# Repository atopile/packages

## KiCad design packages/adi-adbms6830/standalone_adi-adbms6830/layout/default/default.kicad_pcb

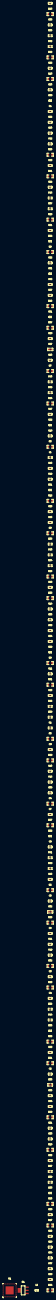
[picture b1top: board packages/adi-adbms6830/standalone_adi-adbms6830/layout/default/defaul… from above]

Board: 2 copper layers, 123 parts (0 on the bottom side), 82 nets, no tracks yet.

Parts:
C1, C2, C3, C4, C5, C6, C7, C8, C9, C10, C11, C12, C13, C14, C15, C16, C17, C18, C19, C20, C21, C22, C23, C24, C25, C26, C27, C28, C29, C30, C31, C32, C33, C34, C35, C36, C37, C38, C39, C40, C41, C42, C43, C44, C45, C46, C47, C48, C49, C50, C53, C54, C55, C56, C60: 0F; C0603
C51, C52, C58, C59, C61: 0F; C0402
C57, C62: 0F; C0805
L1: L 0H; L0603
L2: L0402
Q1: SOT-223-4_L6.5-W3.5-P2.30-LS7.0-BR
R1, R34, R35, R36, R37, R38, R39, R40, R41, R42, R43, R44, R45, R46, R47, R48, R49, R50: 200Ω; R0603
R2, R3, R4, R5, R6, R7, R8, R9, R10, R11, R12, R13, R14, R15, R16, R17, R18, R19, R20, R21, R22, R23, R24, R25, R26, R27, R28, R29, R30, R31, R32, R33: 22Ω; R1206
R51, R52, R53, R54: 49.9Ω; R0402
R55: 1000Ω; R0805
R56: 10Ω; R0402
R57: 330Ω; R1206
U1: QFN-72_L10.0-W10.0-P0.50-BL-EP6.0_1

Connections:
C0: C34.1, C35.2, R34.2, U1.50
C1: C35.1, C36.2, R35.2, U1.48
C2: C36.1, C37.2, R36.2, U1.45
C3: C37.1, C38.2, R37.2, U1.42
C4: C38.1, C39.2, R38.2, U1.39
C5: C39.1, C40.2, R39.2, U1.36
C6: C40.1, C41.2, R40.2, U1.33
C7: C41.1, C42.2, R41.2, U1.30
C8: C1.2, C42.1, R42.2, U1.27
C9: C43.1, C44.2, R43.2, U1.23
C9N: C1.1, C43.2, R1.2, U1.26
C10: C44.1, C45.2, R44.2, U1.20
C11: C45.1, C46.2, R45.2, U1.17
C12: C46.1, C47.2, R46.2, U1.14
C13: C47.1, C48.2, R47.2, U1.11
C14: C48.1, C49.2, R48.2, U1.8
C15: C49.1, C50.2, R49.2, U1.5
C16: C50.1, R50.2, U1.2
DRIVE: R56.1, U1.58
S1N: C2.1, C3.2, R2.2, U1.59
S1P: C3.1, C4.2, R3.2, U1.49
S2N: C4.1, C5.2, R4.2, U1.46
S2P: C5.1, C6.2, R5.2, U1.47
S3N: C6.1, C7.2, R6.2, U1.43
S3P: C7.1, C8.2, R7.2, U1.44
S4N: C8.1, C9.2, R8.2, U1.40
S4P: C9.1, C10.2, R9.2, U1.41
S5N: C10.1, C11.2, R10.2, U1.37
S5P: C11.1, C12.2, R11.2, U1.38
S6N: C12.1, C13.2, R12.2, U1.34
S6P: C13.1, C14.2, R13.2, U1.35
S7N: C14.1, C15.2, R14.2, U1.31
S7P: C15.1, C16.2, R15.2, U1.32
S8N: C16.1, C17.2, R16.2, U1.28
S8P: C17.1, C18.2, R17.2, U1.29
S9N: C18.1, C19.2, R18.2, U1.24
S9P: C19.1, C20.2, R19.2, U1.25
S10N: C20.1, C21.2, R20.2, U1.21
S10P: C21.1, C22.2, R21.2, U1.22
S11N: C22.1, C23.2, R22.2, U1.18
S11P: C23.1, C24.2, R23.2, U1.19
S12N: C24.1, C25.2, R24.2, U1.15
S12P: C25.1, C26.2, R25.2, U1.16
S13N: C26.1, C27.2, R26.2, U1.12
S13P: C27.1, C28.2, R27.2, U1.13
S14N: C28.1, C29.2, R28.2, U1.9
S14P: C29.1, C30.2, R29.2, U1.10
S15N: C30.1, C31.2, R30.2, U1.6
S15P: C31.1, C32.2, R31.2, U1.7
S16N: C32.1, C33.2, R32.2, U1.3
S16P: C33.1, R33.2, U1.4
asic_vp_N: C2.2, C34.2, C51.2, C52.2, C57.2, C58.2, C59.2, C60.2, C61.2, C62.2, R2.1, R34.1, U1.60, U1.73
emitter: L1.1, L2.1, Q1.3
hv: C57.1, R55.2, U1.1
isoSPI_dc_bias_caps[0]-power-hv: C51.1, R51.2, R52.1
isoSPI_dc_bias_caps[1]-power-hv: C52.1, R53.2, R54.1
iso_a_internal_N: C54.1, R52.2, U1.51
iso_a_internal_P: C53.1, R51.1, U1.52
iso_b_internal_N: C56.1, R54.2, U1.55
iso_b_internal_P: C55.1, R53.1, U1.56
sense_filters[1]-cell_power-hv: R3.1, R4.1, R35.1
sense_filters[2]-cell_power-hv: R5.1, R6.1, R36.1
sense_filters[3]-cell_power-hv: R7.1, R8.1, R37.1
sense_filters[4]-cell_power-hv: R9.1, R10.1, R38.1
sense_filters[5]-cell_power-hv: R11.1, R12.1, R39.1
sense_filters[6]-cell_power-hv: R13.1, R14.1, R40.1
sense_filters[7]-cell_power-hv: R15.1, R16.1, R41.1
sense_filters[8]-cell_power-hv: R1.1, R17.1, R18.1, R42.1
sense_filters[9]-cell_power-hv: R21.1, R22.1, R44.1
sense_filters[9]-cell_power-hv-1: R19.1, R20.1, R43.1
sense_filters[11]-cell_power-hv: R23.1, R24.1, R45.1
sense_filters[12]-cell_power-hv: R25.1, R26.1, R46.1
sense_filters[13]-cell_power-hv: R27.1, R28.1, R47.1
sense_filters[14]-cell_power-hv: R29.1, R30.1, R48.1
sense_filters[15]-cell_power-hv: R31.1, R32.1, R49.1
sense_filters[15]-cell_power-hv-1: R33.1, R50.1
vbat-hv: R55.1, R57.1
vref1_cap-power-hv: C58.1, U1.63
vref2_cap-power-hv: C59.1, U1.61
vreg_cap-power-hv: C60.1, L1.2, L2.2, U1.62
vreg_drive_c-power-hv: C61.1, Q1.1, R56.2
vreg_input_c-power-hv: C62.1, Q1.2, Q1.4, R57.2

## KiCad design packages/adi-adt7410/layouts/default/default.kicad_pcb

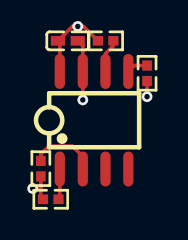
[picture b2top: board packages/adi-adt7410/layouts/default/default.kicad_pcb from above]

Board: 2 copper layers, 6 parts (0 on the bottom side), 6 nets.

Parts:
C1: 100nF ±10% 16V X7R; C0402
R1, R2, R3, R4: 10kΩ ±1% 62.5mW; R0402
U1: SOIC-8_L5.0-W4.0-P1.27-LS6.0-BL

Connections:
CT: R1.2, U1.6
INT: R2.2, U1.5
SCL: R3.1, U1.1
SDA: R4.1, U1.2
gnd: C1.2, U1.7
hv: C1.1, R1.1, R2.1, R3.2, R4.2, U1.8

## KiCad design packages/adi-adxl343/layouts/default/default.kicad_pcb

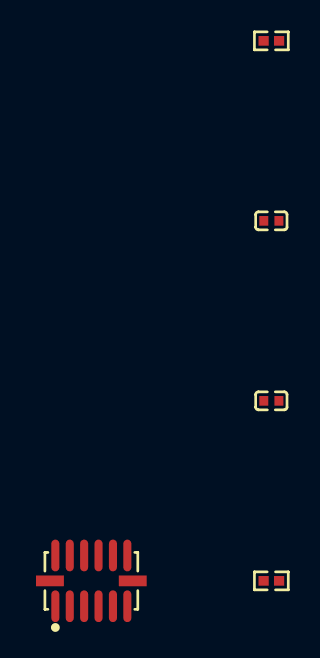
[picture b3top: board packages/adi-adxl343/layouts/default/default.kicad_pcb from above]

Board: 2 copper layers, 5 parts (0 on the bottom side), 6 nets, no tracks yet.

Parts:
C1, C2: 100nF; C0402
R1, R2: 10kΩ; R0402
U1: LGA-14_L5.0-W3.0-P0.80-BL

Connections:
RESERVED: U1.3, U1.11
SCL: R1.2, U1.14
SDA: R2.2, U1.13
decoupling_caps[1]-power-hv: C2.1, R1.1, R2.1, U1.1, U1.7
hv: C1.1, U1.6
lv: C1.2, C2.2, U1.2, U1.4, U1.5, U1.12

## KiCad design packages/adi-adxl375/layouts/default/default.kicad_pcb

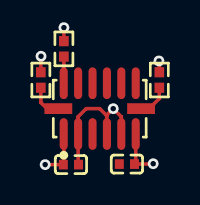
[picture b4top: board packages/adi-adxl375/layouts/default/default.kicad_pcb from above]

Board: 2 copper layers, 6 parts (0 on the bottom side), 6 nets.

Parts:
C1, C2: 0F; C0402
R1: 10000Ω; R0402
R2, R3: 4700Ω; R0402
U1: LGA-14_L5.0-W3.0-P0.80-BL

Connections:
RESERVED: U1.3, U1.11
SCL: R2.1, U1.14
SDA: R3.1, U1.13
hv: C1.1, C2.1, R1.2, R2.2, R3.2, U1.1, U1.6
lv: C1.2, C2.2, U1.2, U1.4, U1.5, U1.12
nCS: R1.1, U1.7
